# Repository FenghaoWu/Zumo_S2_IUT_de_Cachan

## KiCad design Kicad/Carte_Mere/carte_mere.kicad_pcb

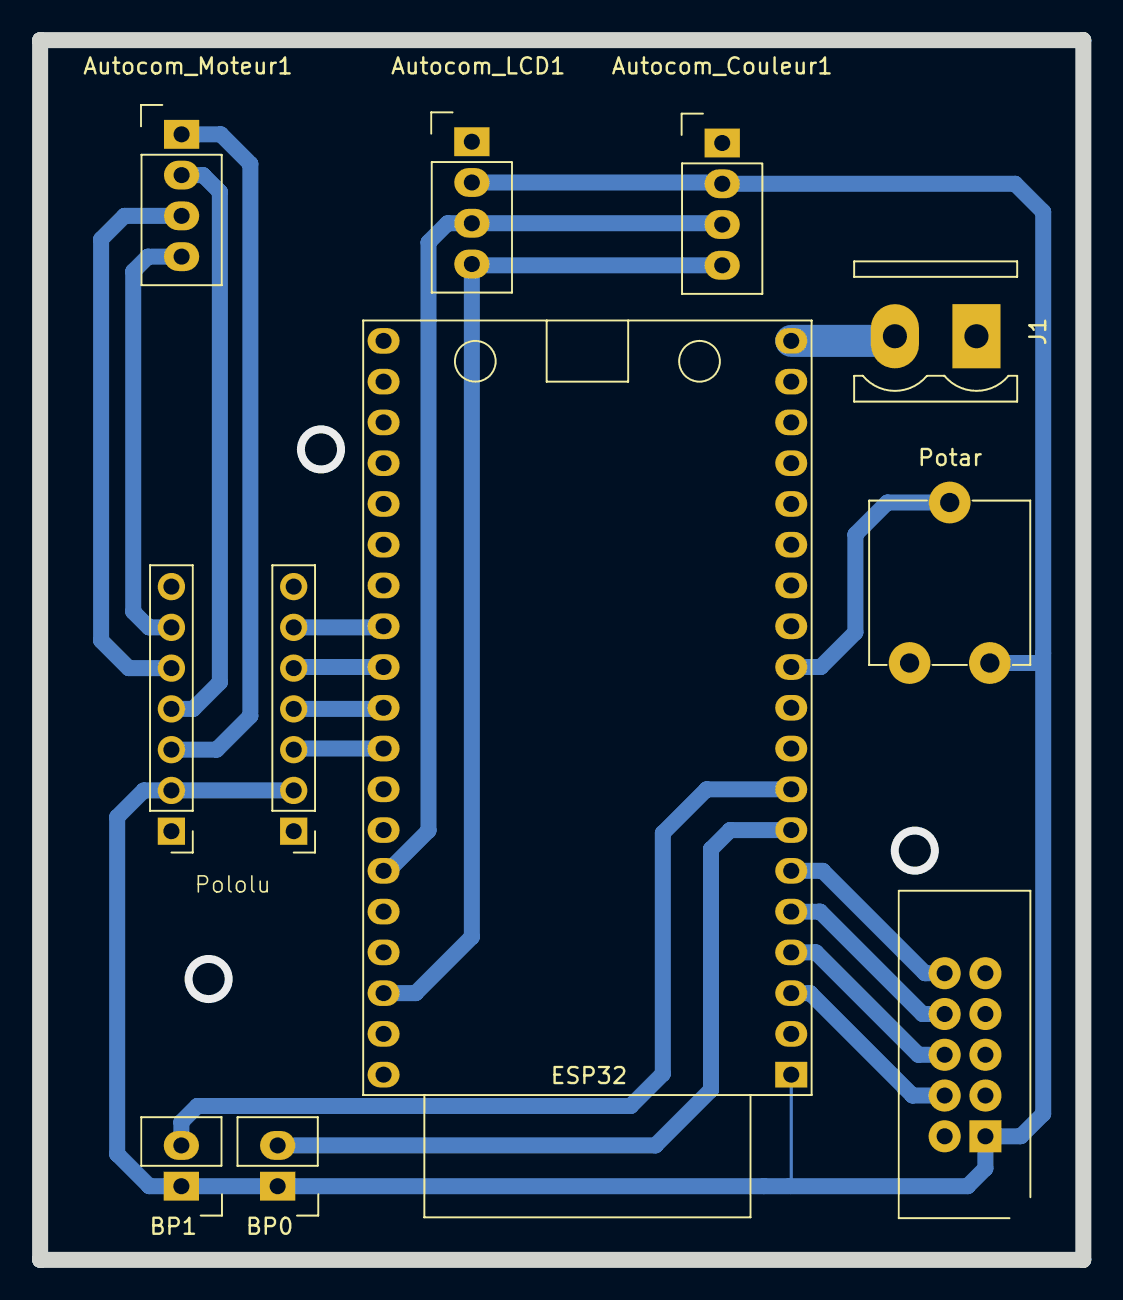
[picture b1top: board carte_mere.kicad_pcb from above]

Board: 2 copper layers, 65.0 x 76.0 mm, 10 parts (0 on the bottom side), 20 nets.

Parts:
Autocom_Couleur1: Autocom4
Autocom_LCD1: Autocom4
Autocom_Moteur1: Autocom4
BP0, BP1: Autocom2
ESP32: ESP32_Module_38_pins_28mm_Wide
J1: Alimentation; OmnimateSL-5,08_1x02_P5.08mm_Vertical
J3: HE10 (provenance); HE10_2x05_P2.54mm
Pololu: Pololu_DRV8835
Potar: Rpot; Potentiometer_ACP_CA9-V10_Vertical

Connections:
3V3: Autocom_Couleur1.2, Autocom_LCD1.2, BP0.1, BP1.1, ESP32.1 (3.3V), J3.1, Pololu.2 (VCC/3.3V), Pololu.13 (VIN), Potar.1
CNY DE: ESP32.6 (GPIO35), J3.10
CNY DI: ESP32.5 (GPIO34), J3.8
CNY GE: ESP32.3 (VP), J3.4
CNY GI: ESP32.4 (VN), J3.6
GND: Autocom_Couleur1.1, Autocom_LCD1.1, ESP32.14 (GND), ESP32.32 (GND), ESP32.38 (GND), J1.1, J3.2, Pololu.1 (GND), Pololu.14 (GND), Potar.3
Hacheur D: ESP32.28 (GPIO17), Pololu.5 (AIN2/AENABLE)
Hacheur G: ESP32.30 (GPIO18), Pololu.3 (BIN2/BENABLE)
Hacheur PWM D: ESP32.27 (GPIO16), Pololu.6 (AIN1/APHASE)
Hacheur PWM G: ESP32.29 (GPIO05), Pololu.4 (BIN1/BPHASE)
unnamed: Autocom_Couleur1.3, Autocom_LCD1.3, ESP32.33 (GPIO21)
unnamed: Autocom_Couleur1.4, Autocom_LCD1.4, ESP32.36 (GPIO22)
unnamed: Autocom_Moteur1.1, Pololu.12 (BOUT2)
unnamed: Autocom_Moteur1.2, Pololu.11 (BOUT1)
unnamed: Autocom_Moteur1.3, Pololu.10 (AOUT2)
unnamed: Autocom_Moteur1.4, Pololu.9 (AOUT1)
unnamed: BP0.2, ESP32.7 (GPIO32)
unnamed: BP1.2, ESP32.8 (GPIO33)
unnamed: ESP32.19 (5V), J1.2
unnamed: ESP32.11 (GPIO27), Potar.2

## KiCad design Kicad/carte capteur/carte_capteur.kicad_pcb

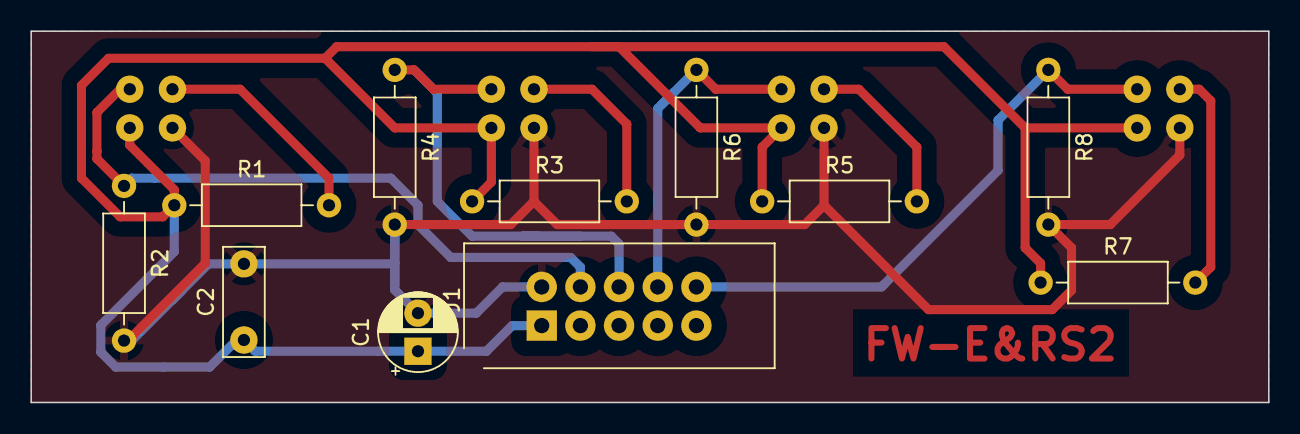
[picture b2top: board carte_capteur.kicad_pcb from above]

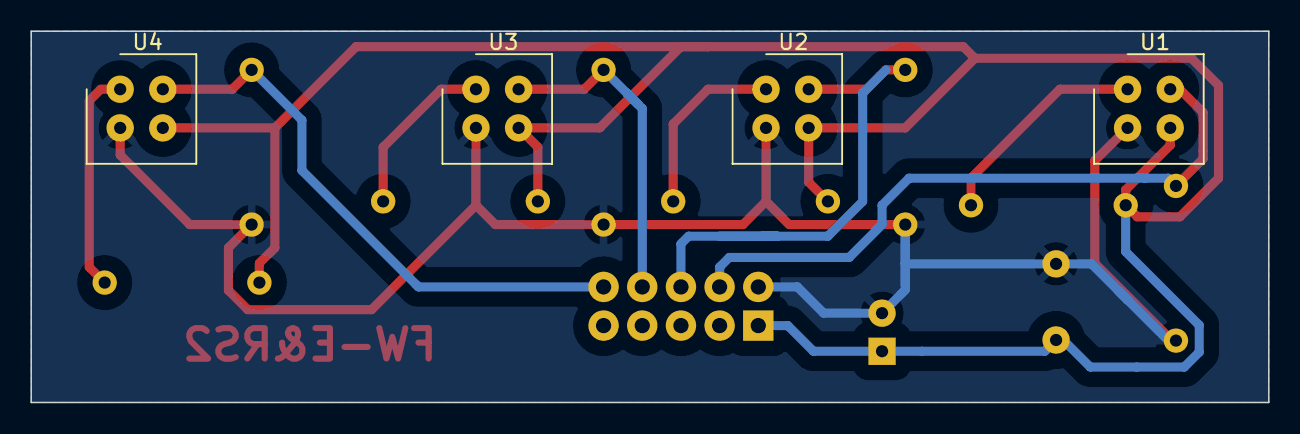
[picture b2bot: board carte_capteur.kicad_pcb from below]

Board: 2 copper layers, 81.3 x 24.4 mm, 15 parts (4 on the bottom side), 10 nets.

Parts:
C1: Cp; CP_Radial_D5.0mm_P2.50mm
C2: C; C_Rect_L7.0mm_W2.5mm_P5.00mm
J1: HE10_02x05; HE10_2x05_P2.54mm
R1, R2, R3, R4, R5, R6, R7, R8: R; R_Axial_DIN0207_L6.3mm_D2.5mm_P10.16mm_Horizontal
U1, U2, U3, U4: CNY70; Vishay_CNY70

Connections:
+3V3: C1.1, C2.1, J1.1, R1.1, R3.1, R5.1, R7.1, U1.3 (C), U2.3 (C), U3.3 (C), U4.3 (C)
/EXTD: J1.10, R8.1, U4.4 (E)
/EXTG: J1.4, R2.1, U1.4 (E)
/INTD: J1.8, R6.1, U3.4 (E)
/INTG: J1.6, R4.1, U2.4 (E)
GND: C1.2, C2.2, J1.2, R2.2, R4.2, R6.2, R8.2, U1.2 (K), U2.2 (K), U3.2 (K), U4.2 (K)
unnamed: R1.2, U1.1 (A)
unnamed: R3.2, U2.1 (A)
unnamed: R5.2, U3.1 (A)
unnamed: R7.2, U4.1 (A)

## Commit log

2025-06-04 Ajout Kicad carte mere + capteur
2025-06-04 Ajout commentaire youssef caca dans main cpp
2025-06-04 Ajout de code test bouton
2025-06-16 Début de la fusion des codes test
2025-06-16 Code_Final_Test_4_CNY70
2025-06-17 Création de bibliothèque moteur
2025-06-17 Code qui vérifie le calibre des capteurs
2025-06-17 Code prêt pour Test de Suivi
2025-06-18 TOR et PWM inversé dans Moteur.h + Compréhension de suivi de ligne avec asservissement de base
2025-06-18 Kd et Kp enfin compris le principe + Avec Youssef on a trouvé 2 valeurs de Kd et Kp qui marchent plutôt bien + Nouvelles valeurs à trouver car imparfait.
2025-06-18 Message test athrur
2025-06-18 Test Arthur Sans Kd
2025-06-18 Programme avec kp et kd mais dans les virages c'est bof je vais retravailler sa demain matin
2025-06-18 je n ai pas touchez kp et kd et j ai rajouter un bout de code pour arreter le robot quand les capteurs exterieur captes
2025-06-19 je pense que la on a quelque chose de pas trop mal avec les réglages kp , kd , vitesse
2025-06-20 kp et kd parfait le robot suit parfaitement la ligne et ne tremble plus !
2025-06-20 VOILA
2025-06-20 code arret station
2025-06-23 Code complet SANS couleur
2025-06-23 Code complet SANS couleur V2
2025-06-23 Code Complet (Sauvegarde) SANS couleur pour test bibliotheque Couleur
2025-06-23 Code Complet avec Couleur SANS Communication
2025-06-23 Code Complet ATTENTE Communication
2025-06-24 Code Final ATTENTE Validation Station
